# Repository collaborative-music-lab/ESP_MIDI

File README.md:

# ESP_MIDI
This repo contains hardware and software components for creating MIDI controllers using the ESP32-s3 microcontroller. The native USB port on the s3 allows for class-compliant MIDI devices which should be recognized natively by any computer.
The repo consists of:
1. **PCB**: A PCB design created in KiCad, along with PDF’s of the board and schematic
2. **Enclosure**: 3d-printable faceplates and knobs
3. **Software**: Arduino-based software for programming your MIDI controller
Each subfolder contains its own readme with additional information for each stage
# FYI / FAQS
There are several things you need to know.
### Allowing for class-compliant midi
To let ESP32-s3 appear as a class compliant device, you *must* set the ‘USB Mode’ for the board as “USB OTG(TinyUSB)”. You can find this setting in the Arduino *Tools* menu.
### Reprogramming after setting USB OTG
Once the board is set to USB OTG mode it won’t show up in Arduino as a Serial device. In order to reprogram the device you must manually hold down the ‘boot’ button on the ESP32-s3, and then press press and release the ‘reset’ on the ESP32-s3.
### Allowing for Serial debugging
In order to use serial.print debugging, you *must* set “USB CDC on boot” to “enabled”. You can find this setting in the Arduino *Tools* menu.

# Components
There are three components to this project:
1. The PCB and electronics assembly
2. The enclosure and mechanical elements
3. The firmware for the ESP-32-S3

Instructions on how to complete the project are in the readme's for these three subfolders.

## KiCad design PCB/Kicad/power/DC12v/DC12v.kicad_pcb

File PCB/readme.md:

# PCB and Electronics Assembly

The project consists of:

1. The main PCB, with the ESP32 pre-soldered
2. 4 potentiometers, 2 to place on the PCB and two additional off-board potentiometers with small pcbs.
3. 4 Arcade Buttons
4. An LSM6DS3 IMU breakout board
5. An RGB LED and resistors

## Assembly

Make sure get your enclosure drilled for your faceplate before you mount your PCB to the faceplate in step 9!!!

1. Place two potentiometers on the PCB. Make sure they are flat. It is a good idea to place the potentiometers on a faceplate to make sure they are aligned. Solder the potentiometers in place.
	* the potentiometers go on the opposite side of the PCB from the ESP32 (e.g. the ESP32 is on the bottom, and the potentiometers are on the top).
2. The LED uses 3 resistors with values between 120 and 470 ohm. All resistors may be the same value. Place and solder the resistors. 
3. DO NOT solder the LED yet. We will solder the PCB once we are ready to mount the electronics to the faceplate.
4. Solder the small PCBs to the two off-board potentiometers. The potentiometer pins go in the holes next to the word 'POT'
5. Solder headers to the LSM6DS3 breakout on the side that has 6 holes. Leave the five holes on the other side of the PCB empty.
6. Place the LSM6DS3 breakout into the head holes labelled 'IMU' on the PCB. Make sure the V+ and VIN pins on the PCB and breakout are aligned. Double-check - if you are not confident, ask for help! 
	* The breakout should be on the bottom of the board, the same side as the ESP32
7. Cut wires for connecting the arcade buttons and external potentiometers. You will need 3 groups with different colors:
	* 6 wires for grounds
	* 6 wires for signal
	* 2 wires for V+
8. Solder these wires into the PCB. Note that there are six places for external sensors, each with a ground, V+, and signal pad. You will need to solder each ground and signal (A1-A6) pad, but only two of the V+/3v pads. 
9. Once all of these wires are soldered in it is time to mount the PCB in the faceplate and solder the LED. 
10. Put the LED in the LED holes. The longest leg of the LED goes into the round hole next to the square hole. If you look on the bottom of the PCB you will see one trace connected to the LED holes - that hole is where the long leg goes. 
	* It is a good idea to plug in your ESP32 and test the LED works before soldering it down
	* you will also need to adjust the LED so it fits through the hold in the faceplate before soldering it.
11. Once the LED is soldered you can screw the potentiometers on the PCB to the faceplate. Use a 10mm socket to screw this down.
12. Place the arcade buttons and other potentiometers in the faceplate. Make sure the faceplate fits inside the enclosure
13. Solder the wires to the potentiometers. Look on the small PCB and you will see indications for where G, V+, and Sig go.
14. Solder wires to the Arcade buttons. These just have a ground and signal wire soldered to the two pins. It doesn't matter which pin is ground and which is signal.
15. You are done soldering! Time to program the ESP32 and test your MIDI controller. You might want to hold off on screwing the faceplate down until you have tested all of the sensors. . .

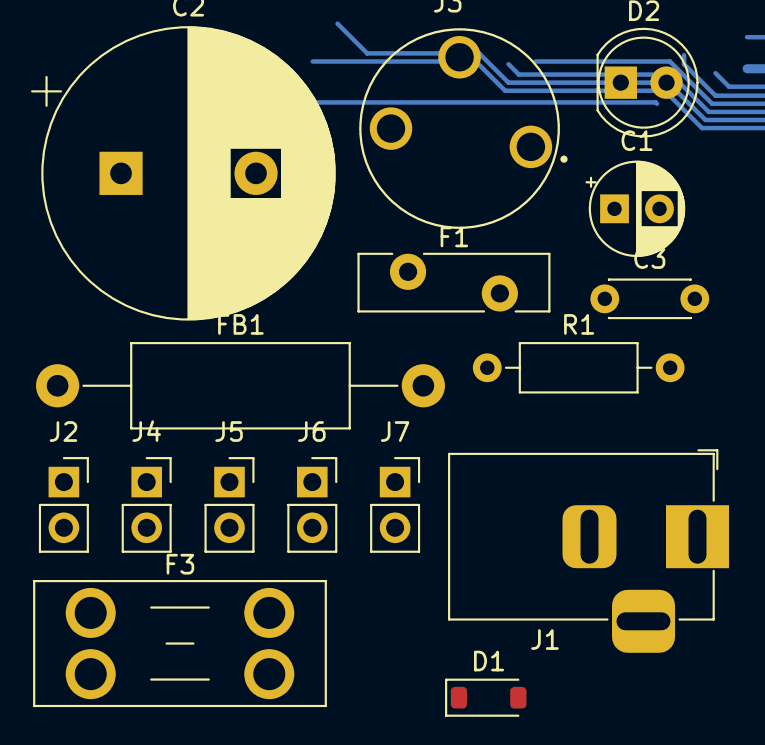
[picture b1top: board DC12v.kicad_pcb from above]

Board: 2 copper layers, 16 parts (0 on the bottom side), 5 nets.

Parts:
C1: 1uF; CP_Radial_D5.0mm_P2.50mm
C2: 3300uF; CP_Radial_D16.0mm_P7.50mm
C3: 0.1uF; C_Disc_D4.3mm_W1.9mm_P5.00mm
D1: TPSMF4L15A; D_SOD-123
D2: LED; LED_D5.0mm
F1: MF-R110; Fuse_Bourns_MF-RG500
F3: Fuse; Fuseholder_Blade_Mini_Keystone_3568
FB1: B82144A2473J; R_Axial_DIN0414_L11.9mm_D4.5mm_P20.32mm_Horizontal
J1: Barrel_Jack_Switch; BarrelJack_Horizontal
J2, J4, J5, J6, J7: Conn_01x02_Pin; PinSocket_1x02_P2.54mm_Vertical
J3: Barrel_Jack_Switch; SWITCHCRAFT_PC722A
R1: R_Small_US; R_Axial_DIN0207_L6.3mm_D2.5mm_P10.16mm_Horizontal

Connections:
+12V: C1.1, C2.1, C3.1, F1.1, F3.2, J2.2, J4.2, J5.2, J6.2, J7.2, R1.1
GND: C1.2, C2.2, C3.2, D1.2 (A), D2.1 (K), J1.2, J2.1, J4.1, J5.1, J6.1, J7.1
unnamed: D1.1 (K), F3.1, J1.1
unnamed: D2.2 (A), R1.2
unnamed: F1.2, FB1.1

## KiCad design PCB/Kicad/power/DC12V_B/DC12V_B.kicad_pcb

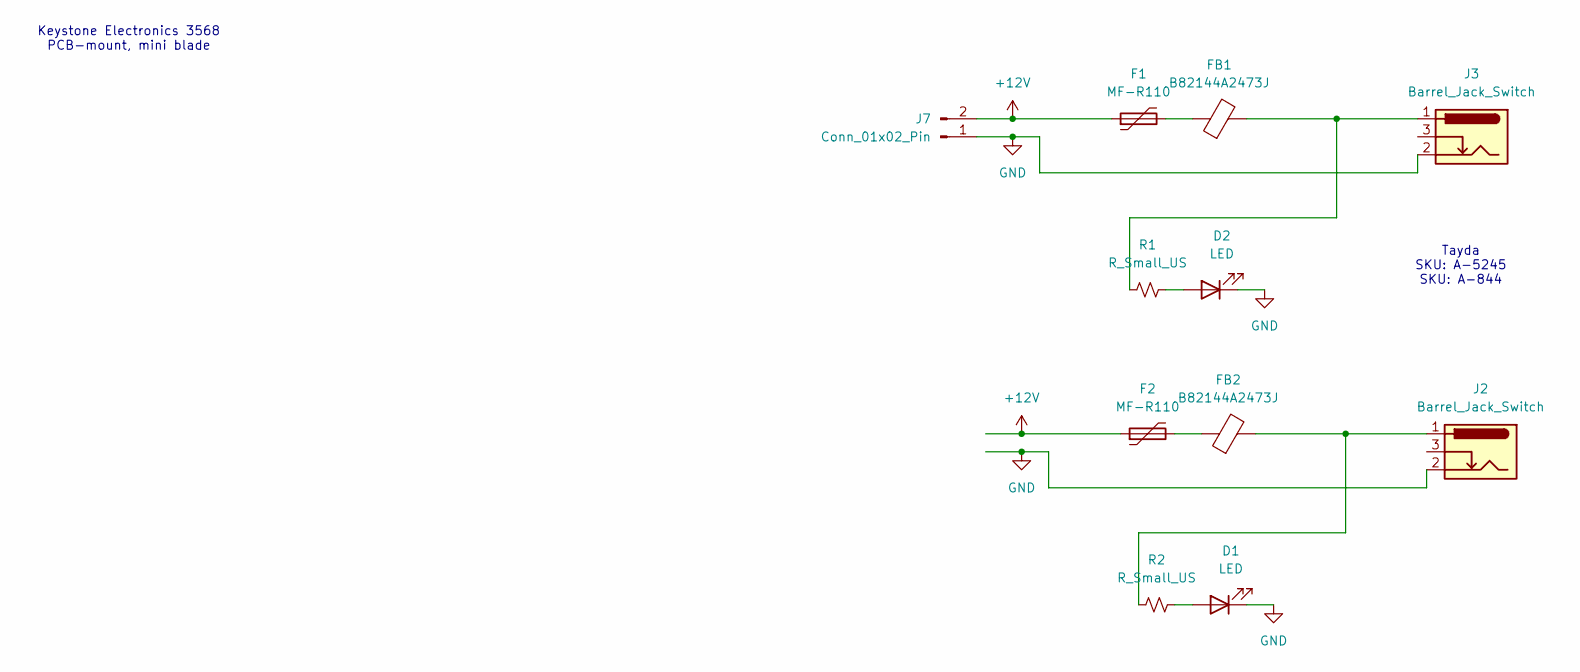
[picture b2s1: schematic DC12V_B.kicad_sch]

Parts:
D1, D2: LED; LED_D5.0mm
F1, F2: MF-R110; Fuse_Bourns_MF-RG500
FB1, FB2: B82144A2473J; R_Axial_DIN0414_L11.9mm_D4.5mm_P20.32mm_Horizontal
J2, J3: Barrel_Jack_Switch; SWITCHCRAFT_PC722A
J7: Conn_01x02_Pin; PinSocket_1x02_P2.54mm_Vertical
R1, R2: R_Small_US; R_Axial_DIN0207_L6.3mm_D2.5mm_P10.16mm_Horizontal

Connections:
+12V: F1.1, F2.1, J7.2
GND: D1.1 (K), D2.1 (K), J2.2, J3.2, J7.1
unnamed: D1.2 (A), R2.2
unnamed: D2.2 (A), R1.2
unnamed: F1.2, FB1.1
unnamed: F2.2, FB2.1
unnamed: FB1.2, J3.1, R1.1
unnamed: FB2.2, J2.1, R2.1

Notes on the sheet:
Tayda SKU: A-5245 SKU: A-844
Keystone Electronics 3568 PCB-mount, mini blade

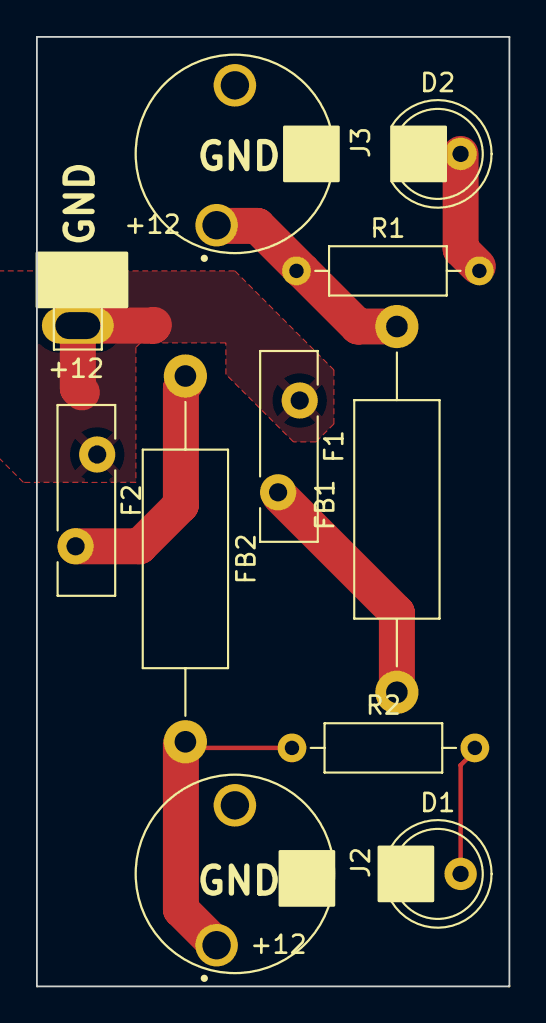
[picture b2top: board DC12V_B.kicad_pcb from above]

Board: 2 copper layers, 26.2 x 52.8 mm, 11 parts (0 on the bottom side), 8 nets.

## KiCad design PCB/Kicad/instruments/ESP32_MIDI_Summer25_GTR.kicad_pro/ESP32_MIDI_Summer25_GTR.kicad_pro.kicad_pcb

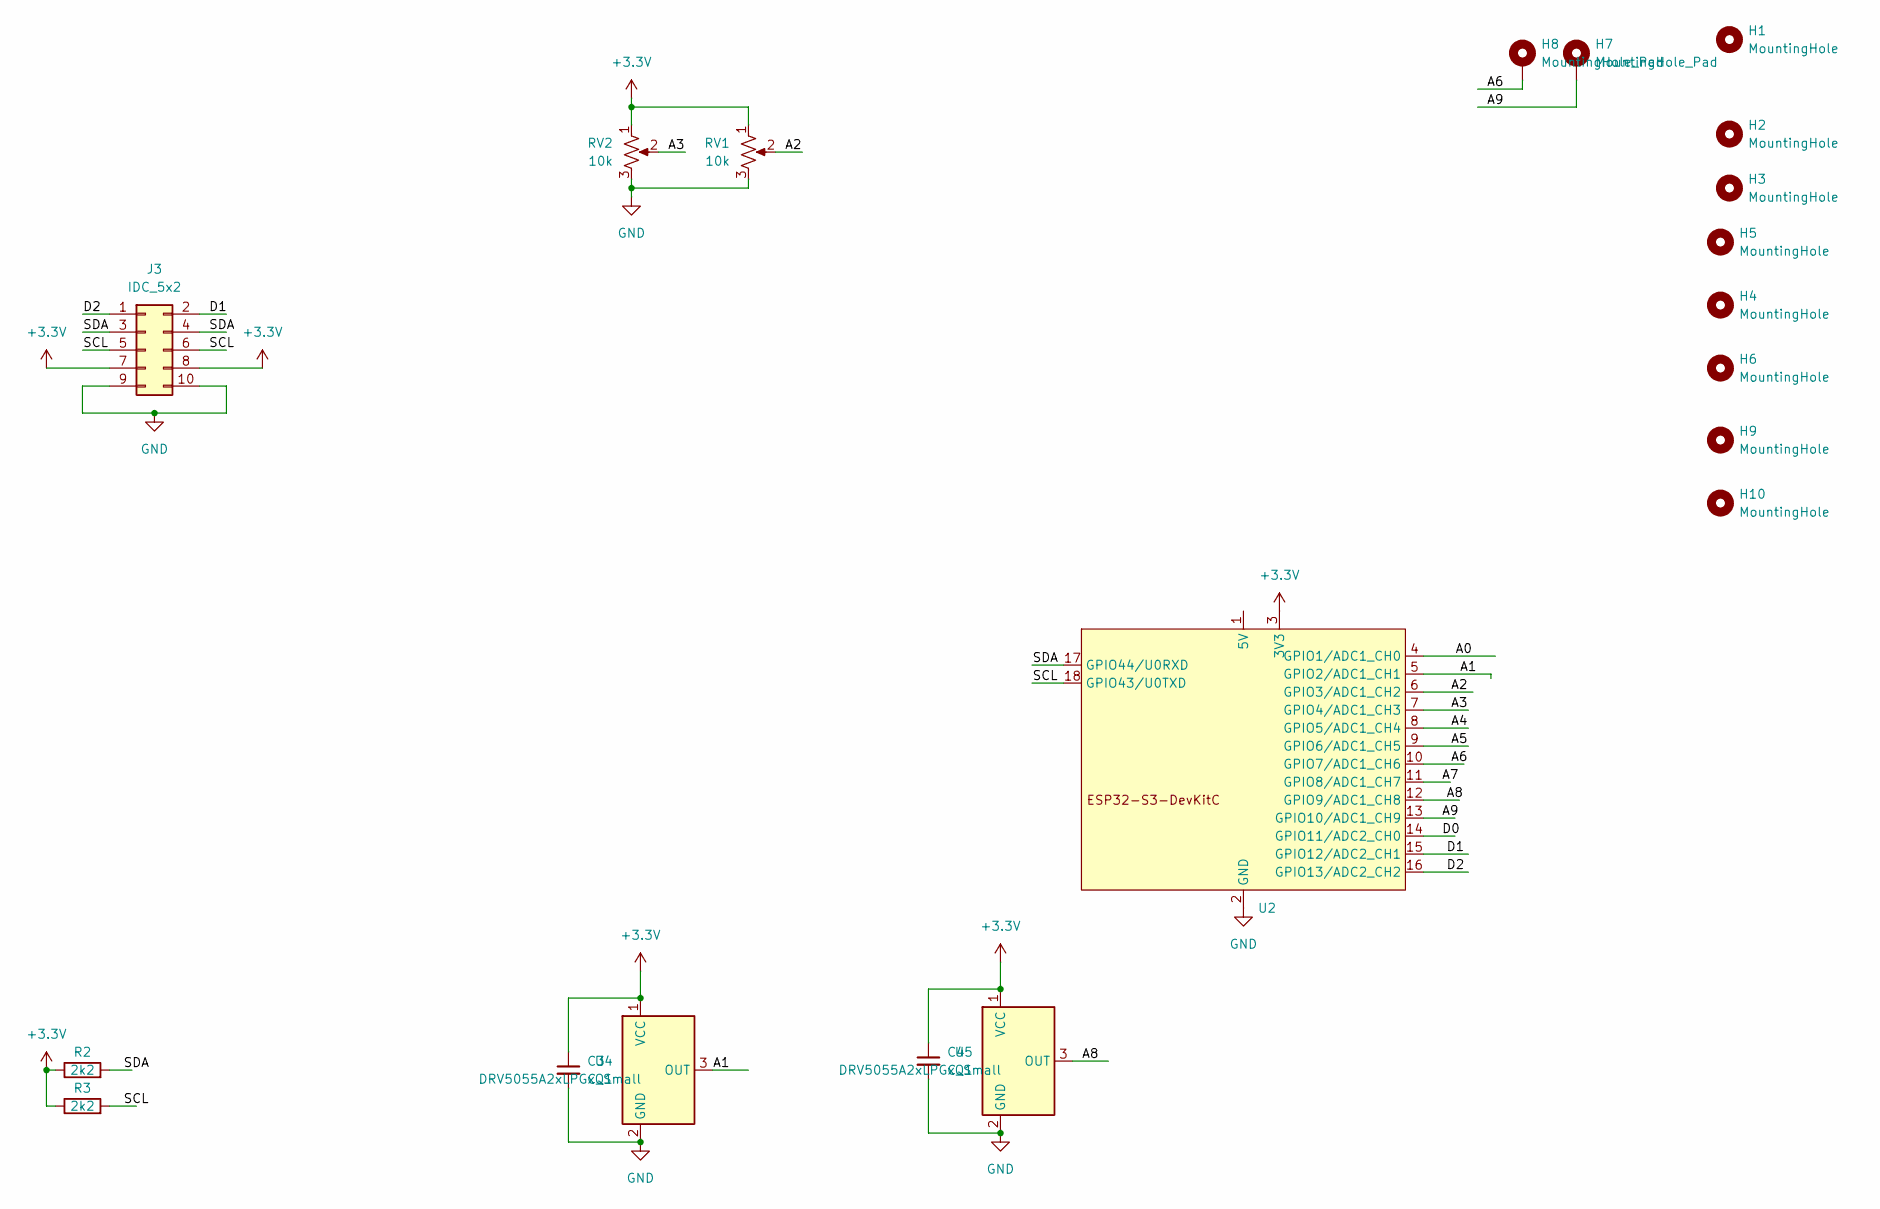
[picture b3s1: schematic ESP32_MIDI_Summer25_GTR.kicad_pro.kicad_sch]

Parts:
C3, C4: C_Small; C_Disc_D6.0mm_W2.5mm_P5.00mm
H1, H2, H3, H5: MountingHole; MountingHole_4.3mm_M4
H4, H6, H9, H10: MountingHole; MountingHole_3.2mm_M3
H7, H8: MountingHole_Pad; MountingHole_6.4mm_M6_DIN965_Pad_TopBottom
J3: IDC_5x2; IDC-Header_2x05_P2.54mm_Vertical
R2, R3: 2k2; R_Axial_DIN0204_L3.6mm_D1.6mm_P7.62mm_Horizontal
RV1, RV2: 10k; Potentiometer_Alps_RK09K_Single_Vertical
U2: Wifiduino-ESP32S3-SMD
U4, U5: DRV5055A2xLPGxQ1; TO-92_flat

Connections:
+3.3V: C3.1, C4.1, J3.7, J3.8, R2.1, R3.1, RV1.1, RV2.1, U2.3 (3V3), U4.1 (VCC), U5.1 (VCC)
/A0: U2.4 (GPIO1/ADC1_CH0)
/A1: U2.5 (GPIO2/ADC1_CH1), U4.3 (OUT)
/A2: RV1.2, U2.6 (GPIO3/ADC1_CH2)
/A3: RV2.2, U2.7 (GPIO4/ADC1_CH3)
/A4: U2.8 (GPIO5/ADC1_CH4)
/A5: U2.9 (GPIO6/ADC1_CH5)
/A6: H8.1, U2.10 (GPIO7/ADC1_CH6)
/A7: U2.11 (GPIO8/ADC1_CH7)
/A8: U2.12 (GPIO9/ADC1_CH8), U5.3 (OUT)
/A9: H7.1, U2.13 (GPIO10/ADC1_CH9)
/D0: U2.14 (GPIO11/ADC2_CH0)
/D1: J3.2, U2.15 (GPIO12/ADC2_CH1)
/D2: J3.1, U2.16 (GPIO13/ADC2_CH2)
/SCL: J3.5, J3.6, R3.2, U2.18 (GPIO43/U0TXD)
/SDA: J3.3, J3.4, R2.2, U2.17 (GPIO44/U0RXD)
GND: C3.2, C4.2, J3.9, J3.10, RV1.3, RV2.3, U2.2 (GND), U4.2 (GND), U5.2 (GND)

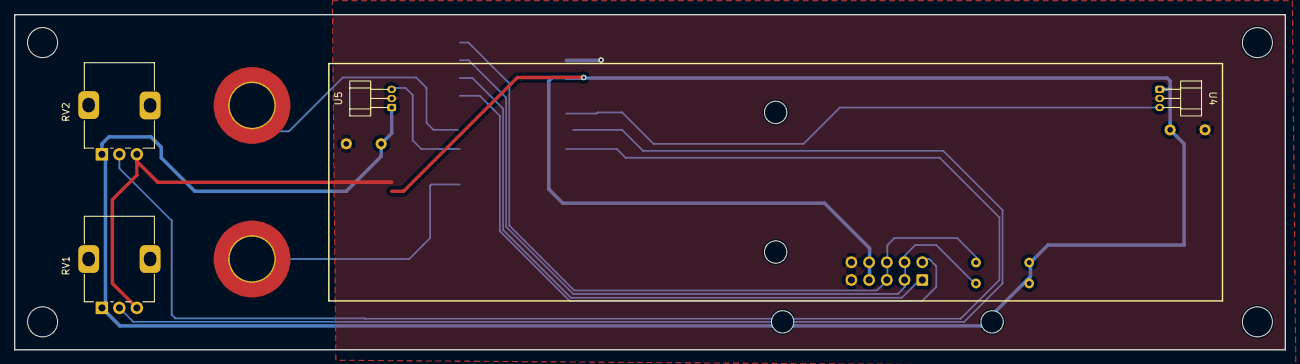
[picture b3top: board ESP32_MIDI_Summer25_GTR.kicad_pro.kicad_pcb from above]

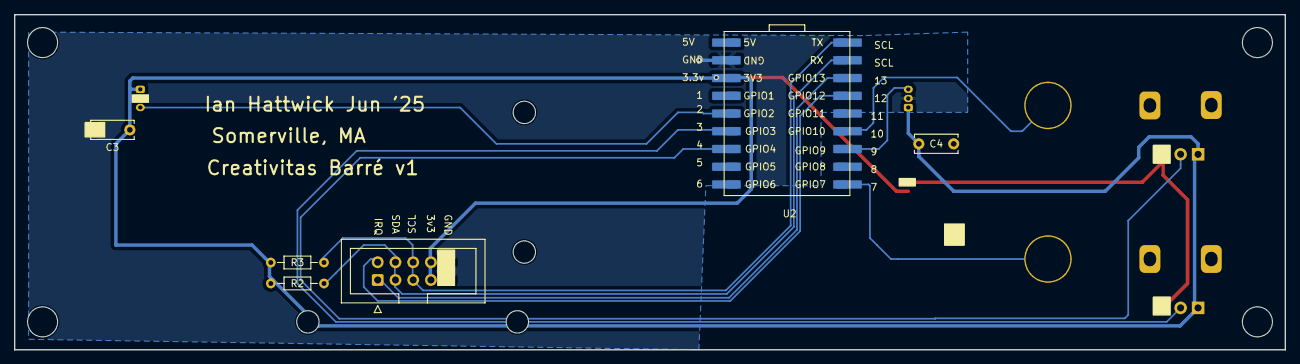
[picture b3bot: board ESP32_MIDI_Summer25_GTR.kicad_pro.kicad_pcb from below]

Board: 2 copper layers, 182.0 x 48.0 mm, 20 parts (6 on the bottom side), 12 nets.

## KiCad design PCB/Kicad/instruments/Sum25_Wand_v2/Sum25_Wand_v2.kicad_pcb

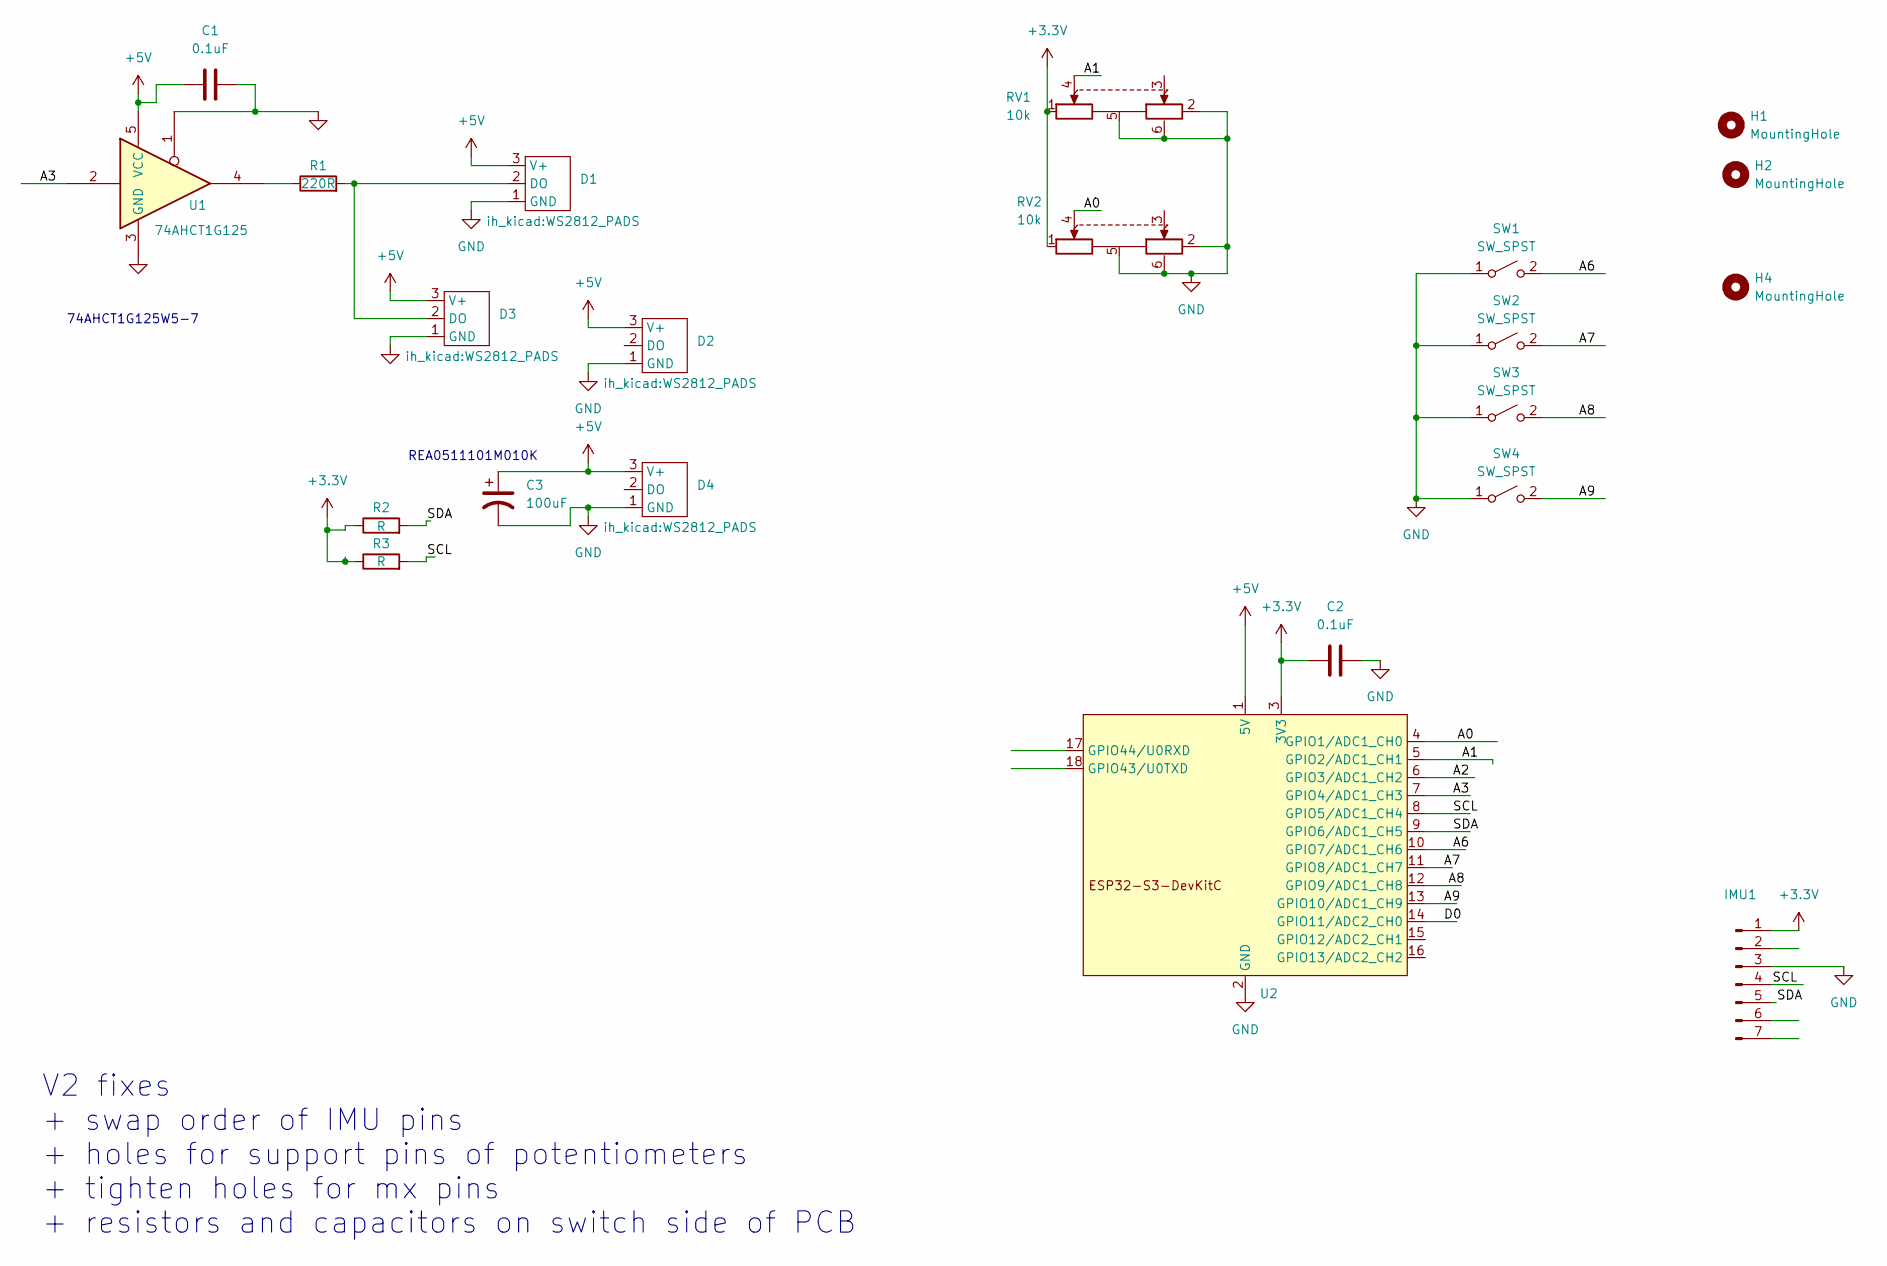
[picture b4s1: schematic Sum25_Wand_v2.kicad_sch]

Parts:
C1, C2: 0.1uF; C_Disc_D5.1mm_W3.2mm_P5.00mm
C3: 100uF; CP_Radial_D5.0mm_P2.00mm
D1, D2, D3, D4: WS2812_PADS
H1, H2, H4: MountingHole; MountingHole_3.2mm_M3
IMU1: Conn_01x07_Pin; PinHeader_1x07_P2.54mm_Vertical
R1: 220R; R_Axial_DIN0204_L3.6mm_D1.6mm_P7.62mm_Horizontal
R2, R3: R; R_Axial_DIN0204_L3.6mm_D1.6mm_P7.62mm_Horizontal
RV1, RV2: 10k; potentiometer_wheel_10mm
SW1, SW2, SW3, SW4: SW_SPST; SW_Cherry_MX_1.00u_Plate
U1: 74AHCT1G125; TSOT-23-5_HandSoldering
U2: Wifiduino-ESP32S3-SMD

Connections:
+3.3V: C2.2, IMU1.1, R2.1, R3.1, RV1.1 (1A), RV2.1 (1A), U2.3 (3V3)
+5V: C1.1, C3.1, D1.3 (V+), D2.3 (V+), D3.3 (V+), D4.3 (V+), U1.5 (VCC), U2.1 (5V)
/A0: RV2.4 (1-Wiper), U2.4 (GPIO1/ADC1_CH0)
/A1: RV1.4 (1-Wiper), U2.5 (GPIO2/ADC1_CH1)
/A2: U2.6 (GPIO3/ADC1_CH2)
/A3: U1.2, U2.7 (GPIO4/ADC1_CH3)
/A6: SW1.2 (B), U2.10 (GPIO7/ADC1_CH6)
/A7: SW2.2 (B), U2.11 (GPIO8/ADC1_CH7)
/A8: SW3.2 (B), U2.12 (GPIO9/ADC1_CH8)
/A9: SW4.2 (B), U2.13 (GPIO10/ADC1_CH9)
/D0: U2.14 (GPIO11/ADC2_CH0)
/SCL: IMU1.4, R3.2, U2.8 (GPIO5/ADC1_CH4)
/SDA: IMU1.5, R2.2, U2.9 (GPIO6/ADC1_CH5)
GND: C1.2, C2.1, C3.2, D1.1 (GND), D2.1 (GND), D3.1 (GND), D4.1 (GND), IMU1.3, RV1.2 (2B), RV1.5 (Common), RV1.6 (Shield), RV2.2 (2B), RV2.5 (Common), RV2.6 (Shield), SW1.1 (A), SW2.1 (A), SW3.1 (A), SW4.1 (A), U1.1, U1.3 (GND), U2.2 (GND)
unnamed: D1.2 (DO), D3.2 (DO), R1.2
unnamed: R1.1, U1.4

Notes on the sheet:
V2 fixes + swap order of IMU pins + holes for support pins of potentiometers + tighten holes for mx pins + resistors and capacitors on switch side of PCB
REA0511101M010K
74AHCT1G125W5-7

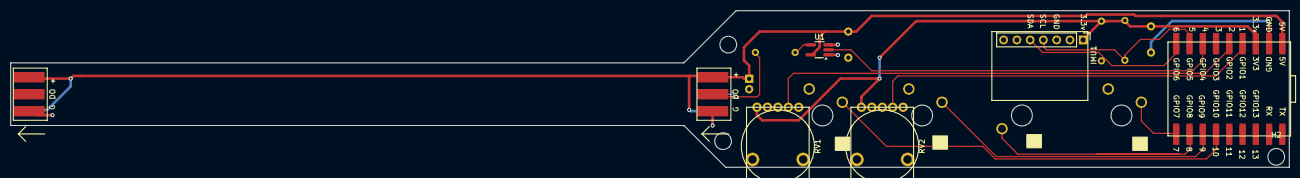
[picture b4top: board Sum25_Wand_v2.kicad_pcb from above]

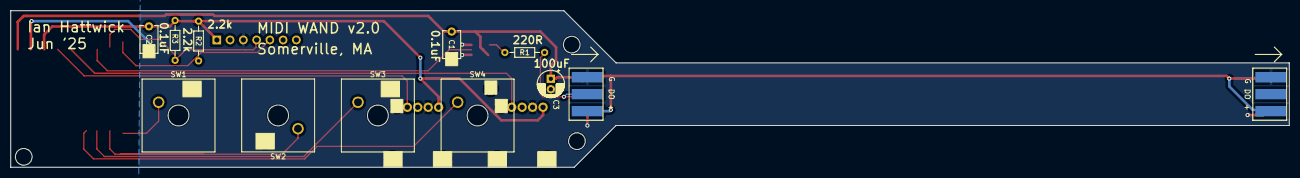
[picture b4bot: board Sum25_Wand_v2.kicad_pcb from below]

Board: 2 copper layers, 245.0 x 30.0 mm, 22 parts (12 on the bottom side), 14 nets.

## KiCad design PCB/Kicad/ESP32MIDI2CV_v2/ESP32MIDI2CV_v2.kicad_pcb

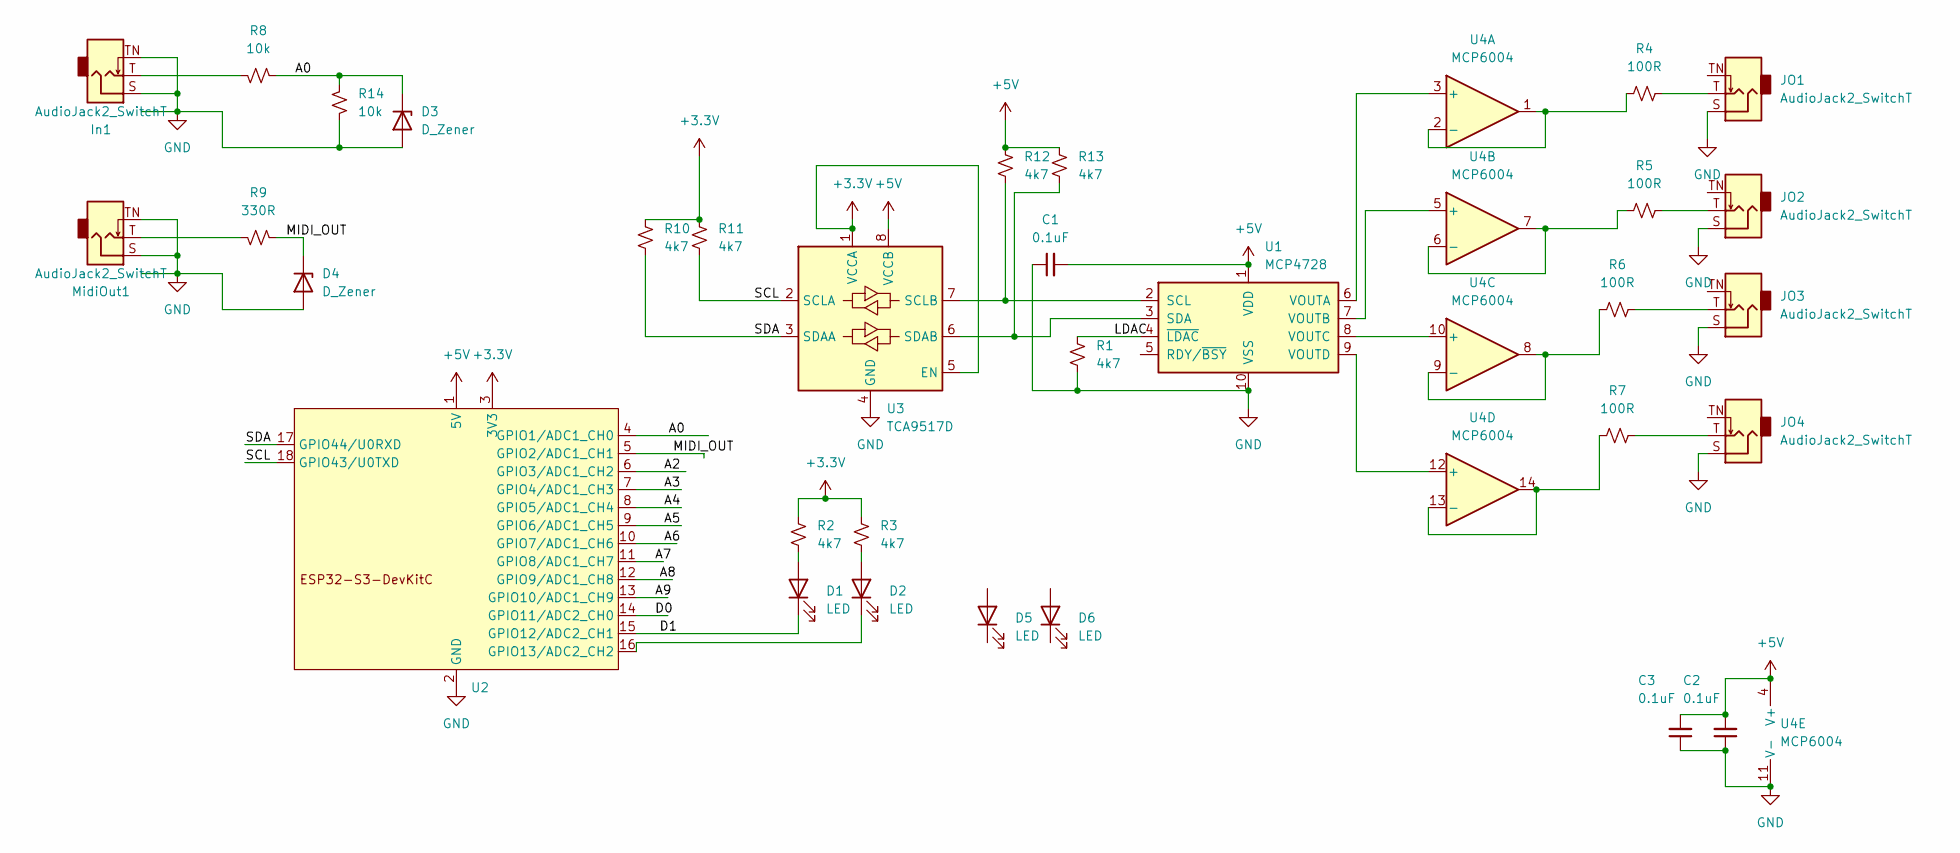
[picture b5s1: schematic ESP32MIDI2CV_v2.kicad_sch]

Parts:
C1, C2, C3: 0.1uF; C_0805_2012Metric_Pad1.18x1.45mm_HandSolder
D1, D2, D5, D6: LED; LED_D3.0mm
D3, D4: D_Zener; D_DO-35_SOD27_P7.62mm_Horizontal
In1: AudioJack2_SwitchT; Jack_3.5mm_QingPu_WQP-PJ398SM_Vertical_CircularHoles
JO1, JO2, JO3, JO4: AudioJack2_SwitchT; Jack_3.5mm_QingPu_WQP-PJ398SM_Vertical_CircularHoles
MidiOut1: AudioJack2_SwitchT; Jack_3.5mm_QingPu_WQP-PJ398SM_Vertical_CircularHoles
R1, R2, R3, R10, R11, R12, R13: 4k7; R_0805_2012Metric
R4, R5, R6, R7: 100R; R_0805_2012Metric
R8, R14: 10k; R_0805_2012Metric
R9: 330R; R_0805_2012Metric
U1: MCP4728; MSOP-10_3x3mm_P0.5mm
U2: Wifiduino-ESP32S3-SMD
U3: TCA9517D; SOIC-8_3.9x4.9mm_P1.27mm
U4: MCP6004; SO-14_3.9x8.65mm_P1.27mm

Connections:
+3.3V: R2.1, R3.1, R10.1, R11.1, U2.3 (3V3), U3.1 (VCCA), U3.5 (EN)
+5V: C1.2, C2.2, C3.2, R12.1, R13.1, U1.1 (VDD), U2.1 (5V), U3.8 (VCCB), U4.4 (V+)
/A0: D3.1 (K), R8.1, R14.1, U2.4 (GPIO1/ADC1_CH0)
/A2: U2.6 (GPIO3/ADC1_CH2)
/A3: U2.7 (GPIO4/ADC1_CH3)
/A4: U2.8 (GPIO5/ADC1_CH4)
/A5: U2.9 (GPIO6/ADC1_CH5)
/A6: U2.10 (GPIO7/ADC1_CH6)
/A7: U2.11 (GPIO8/ADC1_CH7)
/A8: U2.12 (GPIO9/ADC1_CH8)
/A9: U2.13 (GPIO10/ADC1_CH9)
/D0: U2.14 (GPIO11/ADC2_CH0)
/D1: D1.1 (K), U2.15 (GPIO12/ADC2_CH1)
/LDAC: R1.1, U1.4 (~LDAC)
/MIDI_OUT: D4.1 (K), R9.1, U2.5 (GPIO2/ADC1_CH1)
/SCL: R11.2, U2.18 (GPIO43/U0TXD), U3.2 (SCLA)
/SDA: R10.2, U2.17 (GPIO44/U0RXD), U3.3 (SDAA)
GND: C1.1, C2.1, C3.1, D3.2 (A), D4.2 (A), In1.S, In1.TN, JO1.S, JO2.S, JO3.S, JO4.S, MidiOut1.S, MidiOut1.TN, R1.2, R14.2, U1.10 (VSS), U2.2 (GND), U3.4 (GND), U4.11 (V-)
unnamed: D1.2 (A), R2.2
unnamed: D2.2 (A), R3.2
unnamed: D2.1 (K), U2.16 (GPIO13/ADC2_CH2)
unnamed: In1.T, R8.2
unnamed: JO1.T, R4.2
unnamed: JO2.T, R5.2
unnamed: JO3.T, R6.2
unnamed: JO4.T, R7.2
unnamed: MidiOut1.T, R9.2
unnamed: R12.2, U1.2 (SCL), U3.7 (SCLB)
unnamed: R13.2, U1.3 (SDA), U3.6 (SDAB)
unnamed: U1.6 (VOUTA), U4.3 (+)
unnamed: U1.7 (VOUTB), U4.5 (+)
unnamed: U1.8 (VOUTC), U4.10 (+)
unnamed: U1.9 (VOUTD), U4.12 (+)
unnamed: R4.1, U4.1, U4.2 (-)
unnamed: R5.1, U4.6 (-), U4.7
unnamed: R6.1, U4.8, U4.9 (-)
unnamed: R7.1, U4.13 (-), U4.14

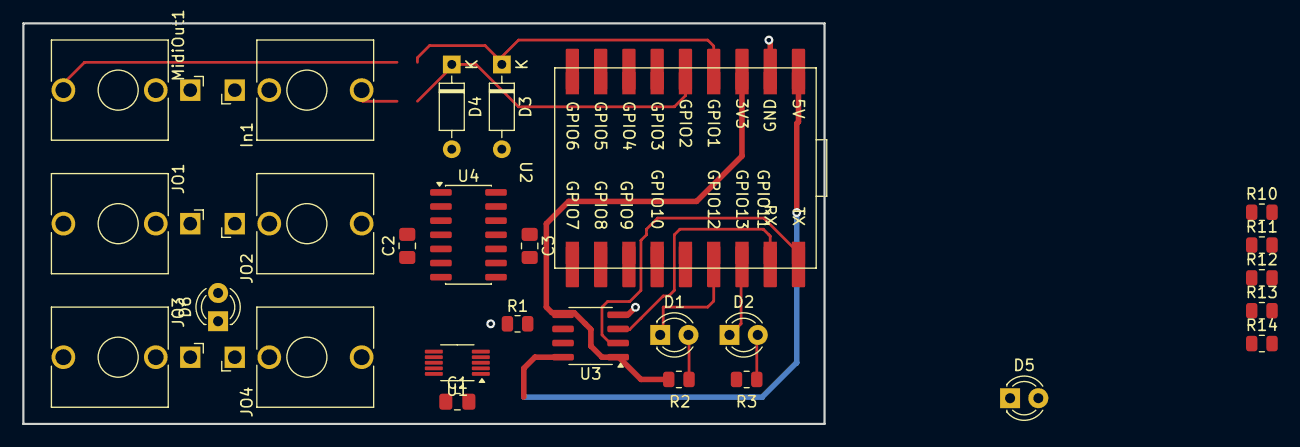
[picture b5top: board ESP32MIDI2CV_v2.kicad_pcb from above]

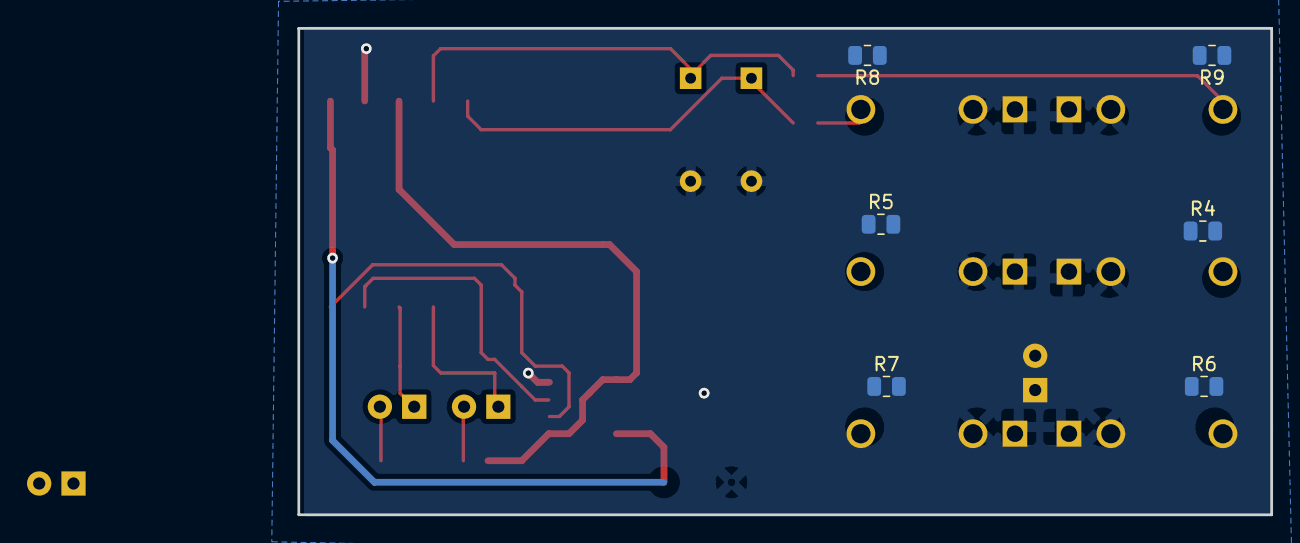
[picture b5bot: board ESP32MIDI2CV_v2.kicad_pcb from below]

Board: 2 copper layers, 72.0 x 36.0 mm, 33 parts (6 on the bottom side), 28 nets.

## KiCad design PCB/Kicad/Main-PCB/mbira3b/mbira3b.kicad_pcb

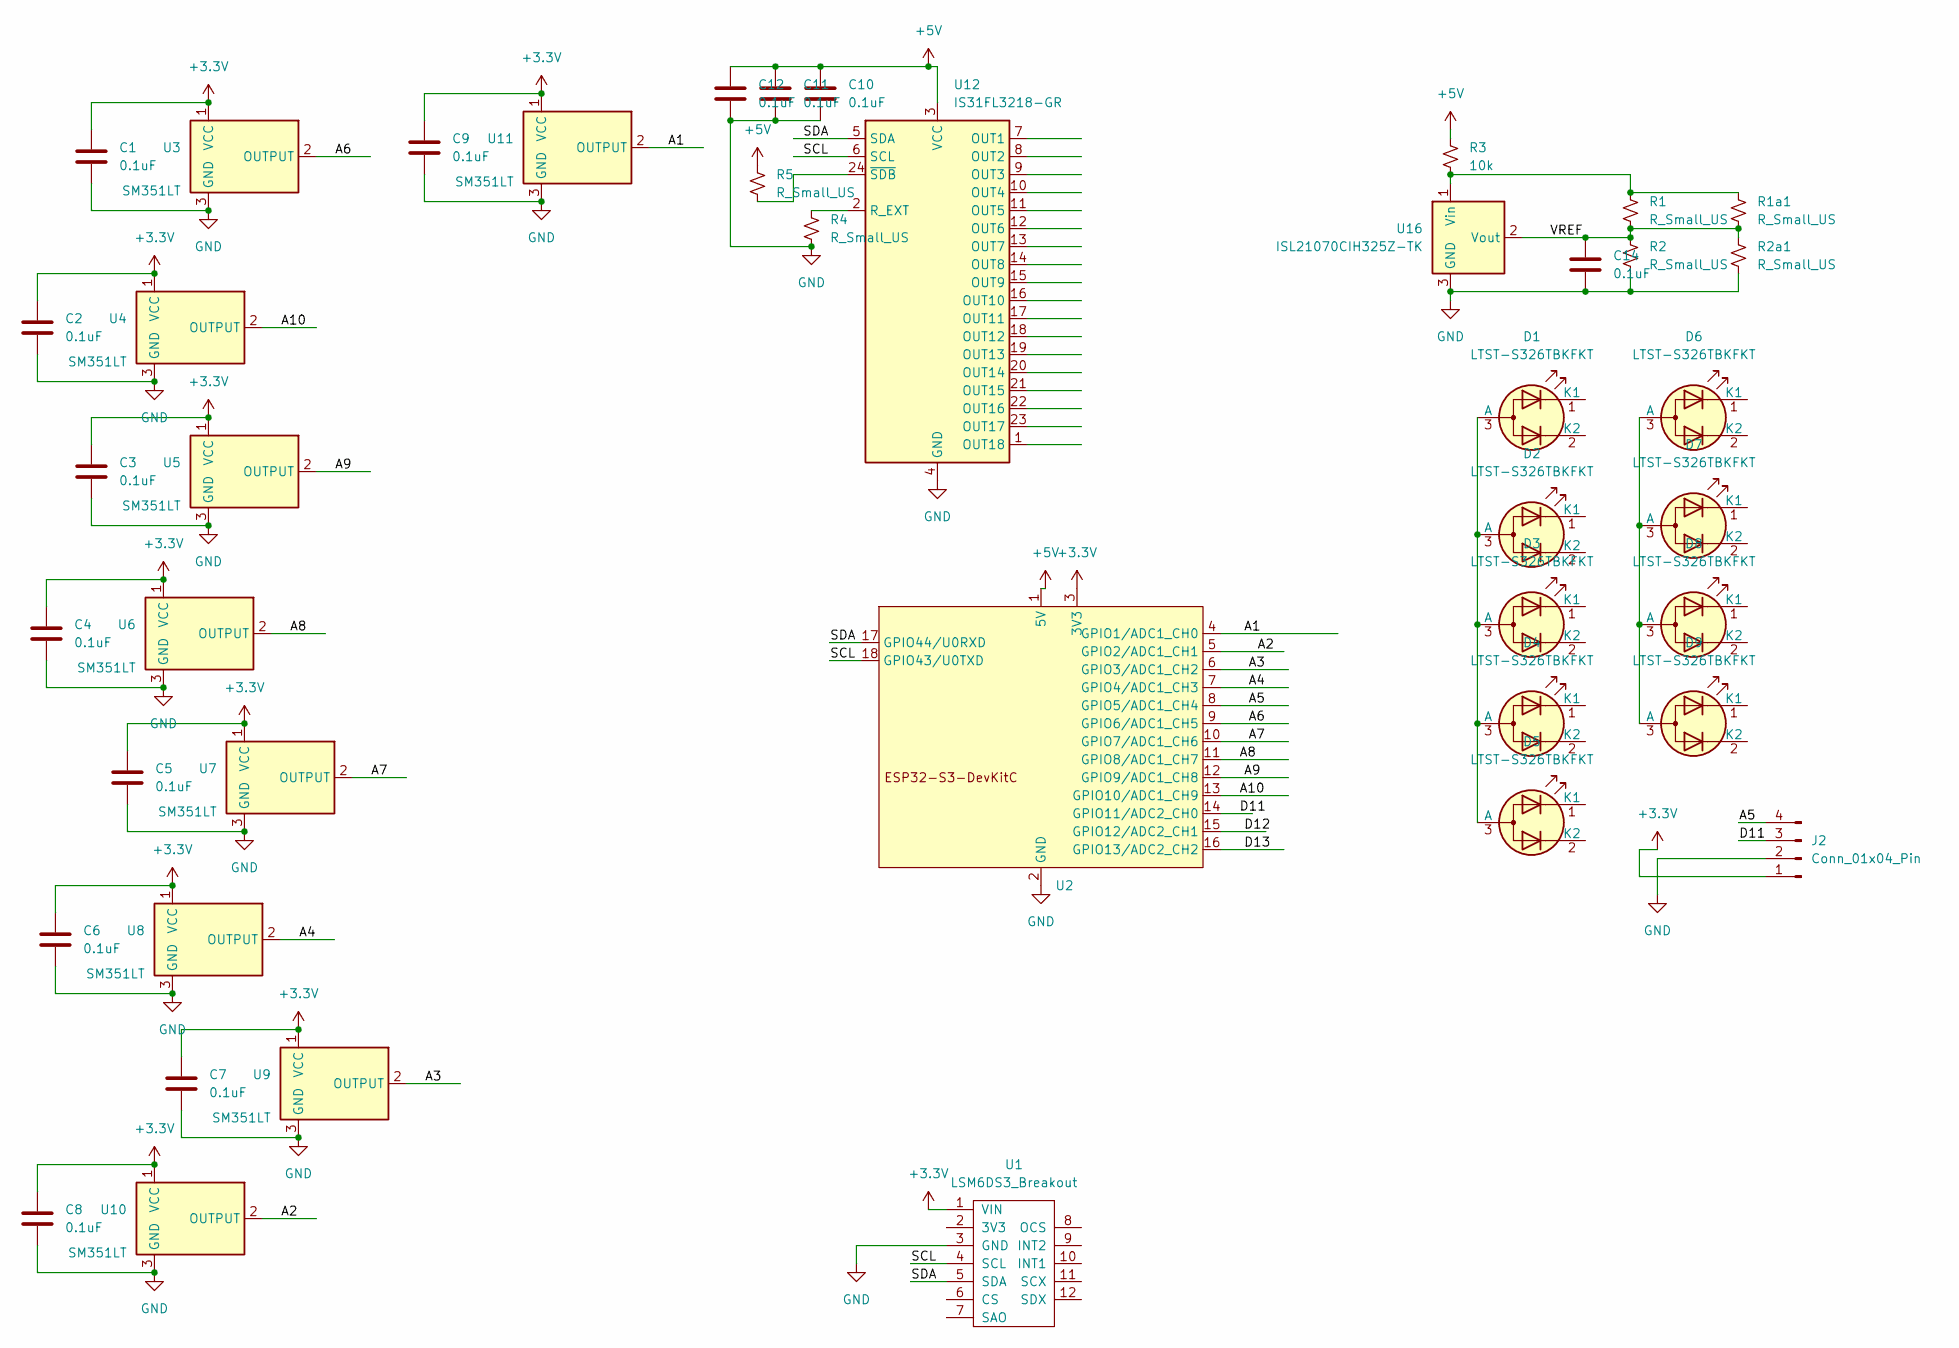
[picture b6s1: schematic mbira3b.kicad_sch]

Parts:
C1, C2, C3, C4, C5, C6, C7, C8, C9, C10, C11, C12, C14: 0.1uF; C_0805_2012Metric_Pad1.18x1.45mm_HandSolder
D1, D2, D3, D4, D5, D6, D7, D8, D9: LTST-S326TBKFKT; LED_LiteOn_LTST-S326
J2: Conn_01x04_Pin; PinHeader_1x04_P1.27mm_Vertical
R1, R2, R4, R5: R_Small_US; R_0805_2012Metric
R1a1, R2a1: R_Small_US; R_Axial_DIN0207_L6.3mm_D2.5mm_P2.54mm_Vertical
R3: 10k; R_0805_2012Metric
U1: LSM6DS3_Breakout; LSM6DS3_Breakout_oneSide
U2: Wifiduino-ESP32S3-SMD
U3, U4, U5, U6, U7, U8, U9, U10, U11: SM351LT; SOT-23
U12: IS31FL3218-GR; SOP-24_7.5x15.4mm_P1.27mm
U16: ISL21070CIH325Z-TK; SOT-23

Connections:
+3.3V: C1.1, C2.1, C3.1, C4.1, C5.1, C6.1, C7.1, C8.1, C9.1, J2.1, U1.1 (VIN), U2.3 (3V3), U3.1 (VCC), U4.1 (VCC), U5.1 (VCC), U6.1 (VCC), U7.1 (VCC), U8.1 (VCC), U9.1 (VCC), U10.1 (VCC), U11.1 (VCC)
+5V: C10.1, C11.1, C12.1, R3.1, R5.1, U2.1 (5V), U12.3 (VCC)
/A1: U2.4 (GPIO1/ADC1_CH0), U11.2 (OUTPUT)
/A2: U2.5 (GPIO2/ADC1_CH1), U10.2 (OUTPUT)
/A3: U2.6 (GPIO3/ADC1_CH2), U9.2 (OUTPUT)
/A4: U2.7 (GPIO4/ADC1_CH3), U8.2 (OUTPUT)
/A5: J2.4, U2.8 (GPIO5/ADC1_CH4)
/A6: U2.9 (GPIO6/ADC1_CH5), U3.2 (OUTPUT)
/A7: U2.10 (GPIO7/ADC1_CH6), U7.2 (OUTPUT)
/A8: U2.11 (GPIO8/ADC1_CH7), U6.2 (OUTPUT)
/A9: U2.12 (GPIO9/ADC1_CH8), U5.2 (OUTPUT)
/A10: U2.13 (GPIO10/ADC1_CH9), U4.2 (OUTPUT)
/D11: J2.3, U2.14 (GPIO11/ADC2_CH0)
/D12: U2.15 (GPIO12/ADC2_CH1)
/D13: U2.16 (GPIO13/ADC2_CH2)
/SCL: U1.4 (SCL), U2.18 (GPIO43/U0TXD), U12.6 (SCL)
/SDA: U1.5 (SDA), U2.17 (GPIO44/U0RXD), U12.5 (SDA)
/VREF: C14.1, R1.2, R1a1.2, R2.1, R2a1.1, U16.2 (Vout)
GND: C1.2, C2.2, C3.2, C4.2, C5.2, C6.2, C7.2, C8.2, C9.2, C10.2, C11.2, C12.2, C14.2, J2.2, R2.2, R2a1.2, R4.2, U1.3 (GND), U2.2 (GND), U3.3 (GND), U4.3 (GND), U5.3 (GND), U6.3 (GND), U7.3 (GND), U8.3 (GND), U9.3 (GND), U10.3 (GND), U11.3 (GND), U12.4 (GND), U16.3 (GND)
unnamed: D1.3 (A), D2.3 (A), D3.3 (A), D4.3 (A), D5.3 (A)
unnamed: D6.3 (A), D7.3 (A), D8.3 (A), D9.3 (A)
unnamed: R4.1, U12.2 (R_EXT)
unnamed: R5.2, U12.24 (~SDB)
unnamed: R1.1, R1a1.1, R3.2, U16.1 (Vin)

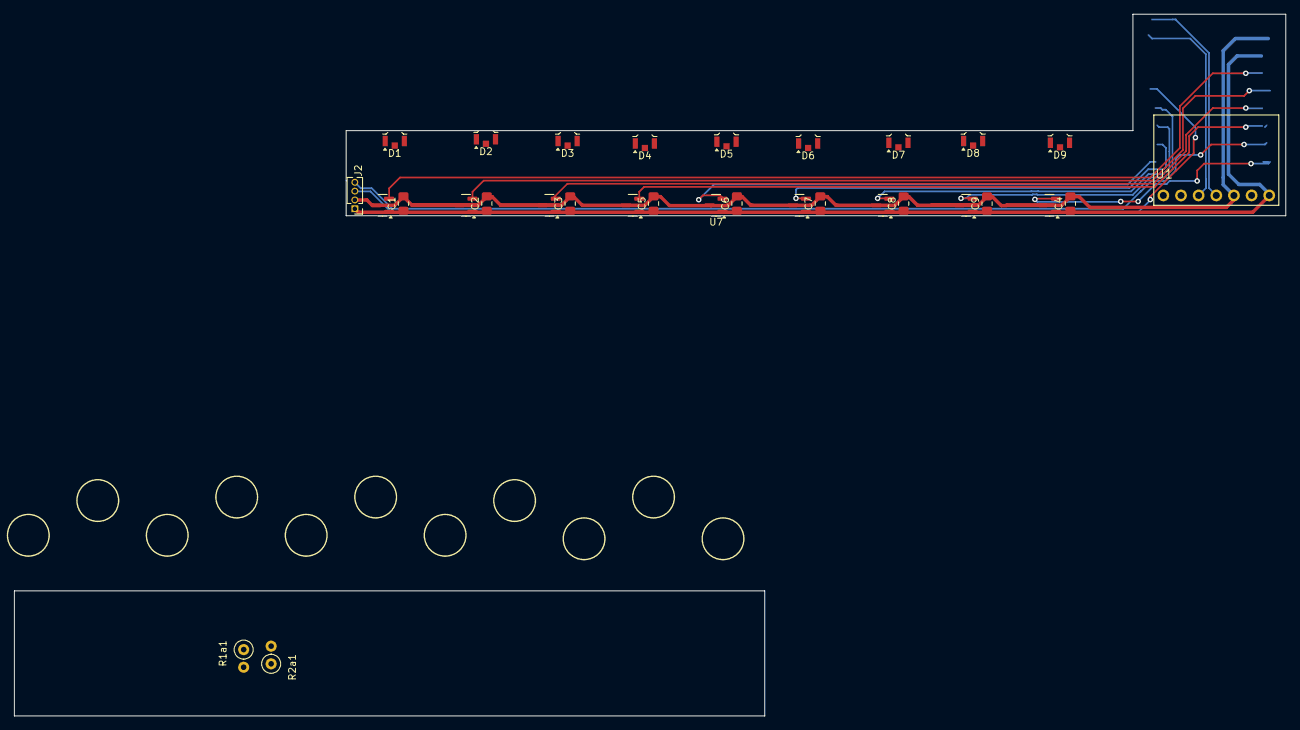
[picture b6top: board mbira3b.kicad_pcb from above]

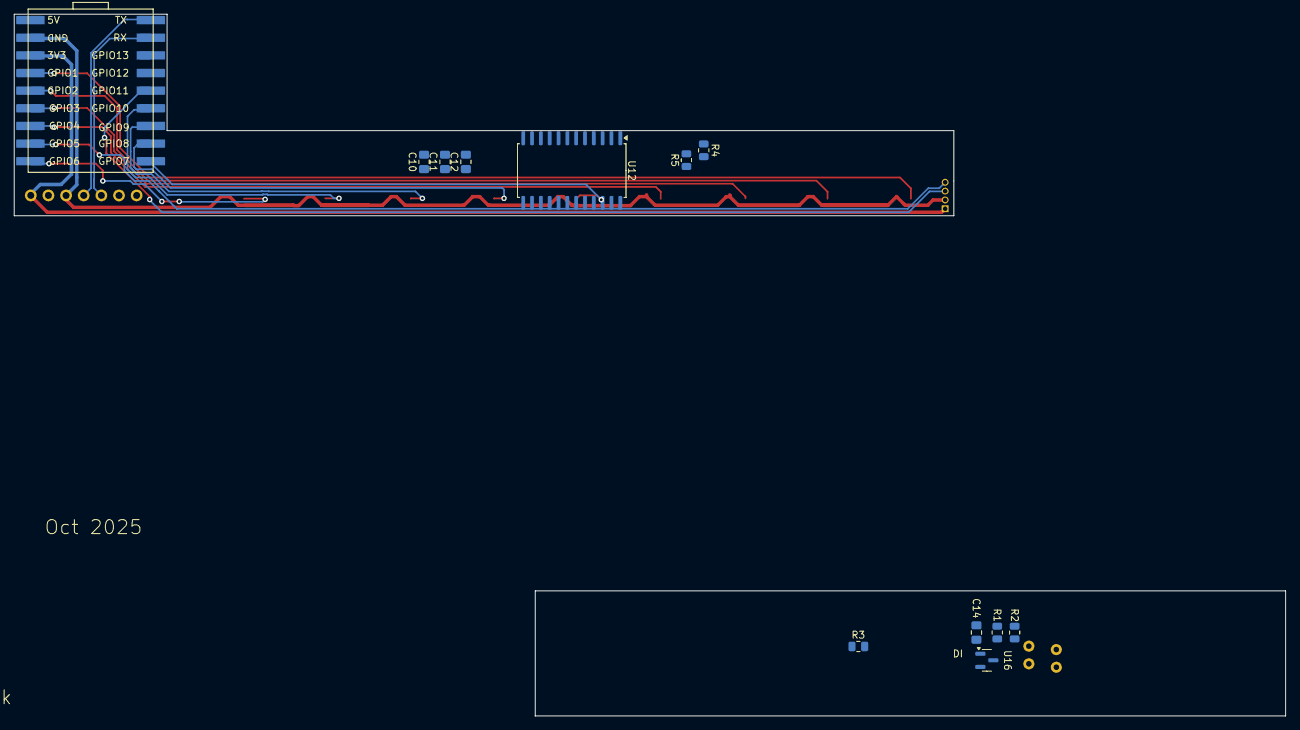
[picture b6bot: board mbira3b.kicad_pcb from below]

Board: 2 copper layers, 135.2 x 29.0 mm, 43 parts (12 on the bottom side), 22 nets.
